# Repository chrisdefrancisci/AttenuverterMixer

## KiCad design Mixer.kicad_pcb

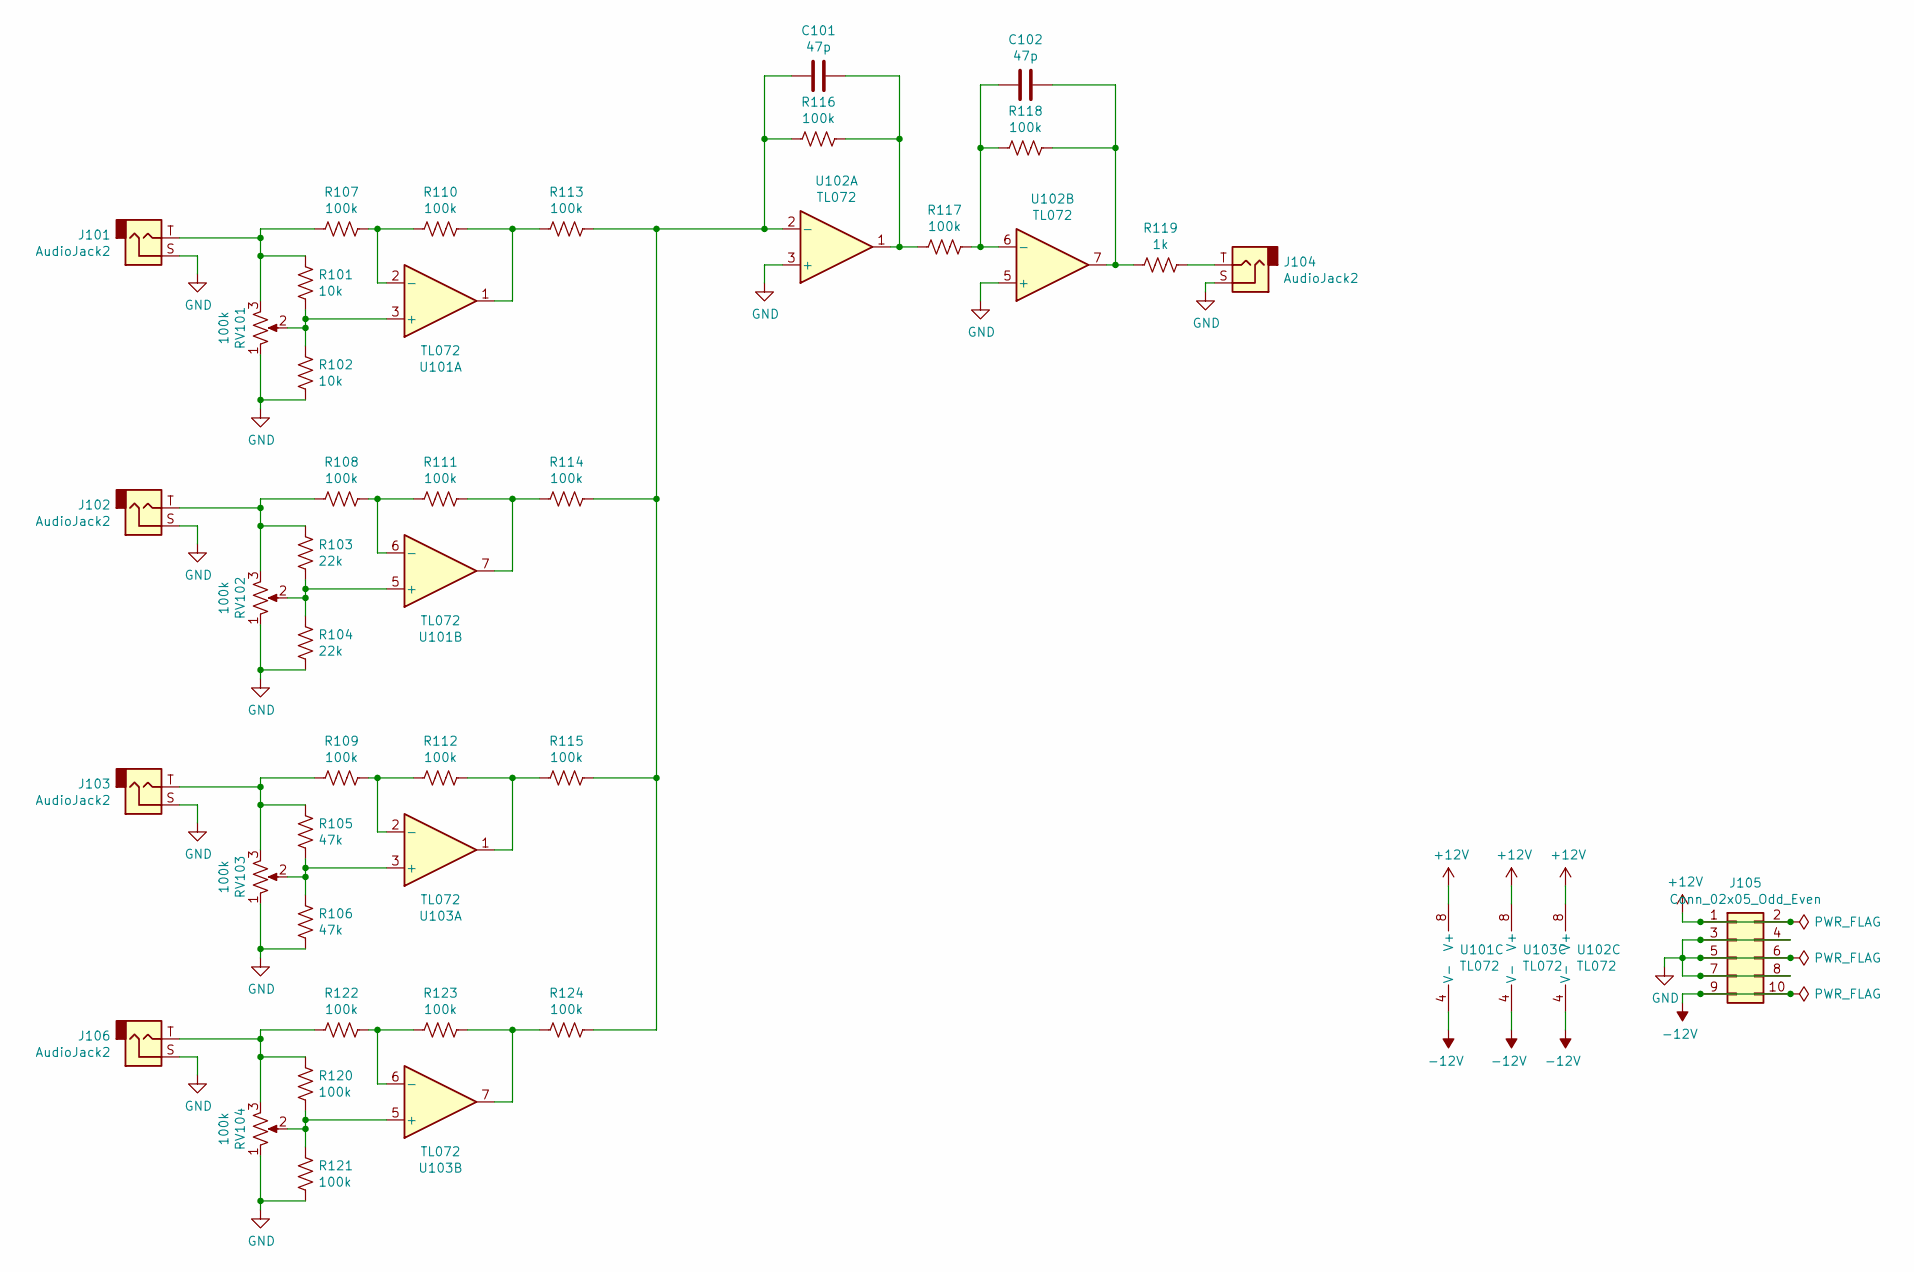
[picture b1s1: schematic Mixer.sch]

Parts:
C101, C102: 47p; C_0402_1005Metric; LCSC C1567
J101, J102, J103, J104, J106: AudioJack2; A-2563
J105: Conn_02x05_Odd_Even; PinHeader_2x05_P2.54mm_Vertical
R101, R102: 10k; R_0805_2012Metric; LCSC C17414
R103, R104: 22k; R_0805_2012Metric; LCSC C17560
R105, R106: 47k; R_0805_2012Metric; LCSC C17713
R107, R108, R109, R110, R111, R112, R113, R114, R115, R116, R117, R118, R120, R121, R122, R123, R124: 100k; R_0805_2012Metric; LCSC C17407
R119: 1k; R_0805_2012Metric; LCSC C17513
RV101, RV102, RV103, RV104: 100k; A-5513
U101, U102, U103: TL072; SOIC-8_3.9x4.9mm_P1.27mm; LCSC C6961

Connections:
+12V: J105.1, J105.2, U101.8 (V+), U102.8 (V+), U103.8 (V+)
-12V: J105.9, J105.10, U101.4 (V-), U102.4 (V-), U103.4 (V-)
GND: J101.S, J102.S, J103.S, J104.S, J105.3, J105.4, J105.5, J105.6, J105.7, J105.8, J106.S, R102.2, R104.2, R106.2, R121.2, RV101.1, RV102.1, RV103.1, RV104.1, U102.3 (+), U102.5 (+)
unnamed: C101.1, R116.1, R117.2, U102.1
unnamed: C101.2, R113.1, R114.1, R115.1, R116.2, R124.1, U102.2 (-)
unnamed: C102.1, R118.1, R119.2, U102.7
unnamed: C102.2, R117.1, R118.2, U102.6 (-)
unnamed: J101.T, R101.1, R107.2, RV101.3
unnamed: J102.T, R103.1, R108.2, RV102.3
unnamed: J103.T, R105.1, R109.2, RV103.3
unnamed: J104.T, R119.1
unnamed: J106.T, R120.1, R122.2, RV104.3
unnamed: R101.2, R102.1, RV101.2, U101.3 (+)
unnamed: R103.2, R104.1, RV102.2, U101.5 (+)
unnamed: R105.2, R106.1, RV103.2, U103.3 (+)
unnamed: R107.1, R110.2, U101.2 (-)
unnamed: R108.1, R111.2, U101.6 (-)
unnamed: R109.1, R112.2, U103.2 (-)
unnamed: R110.1, R113.2, U101.1
unnamed: R111.1, R114.2, U101.7
unnamed: R112.1, R115.2, U103.1
unnamed: R120.2, R121.1, RV104.2, U103.5 (+)
unnamed: R122.1, R123.2, U103.6 (-)
unnamed: R123.1, R124.2, U103.7

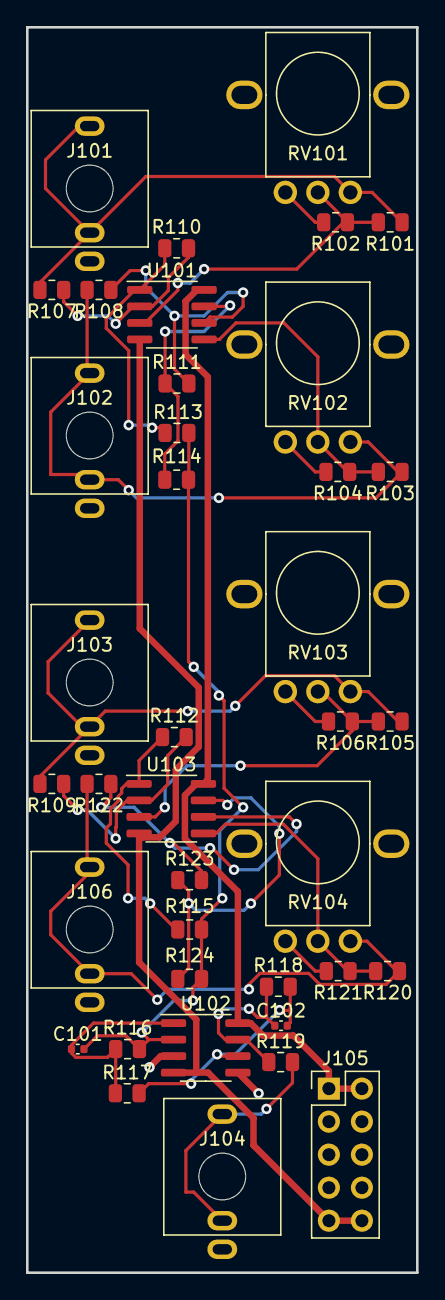
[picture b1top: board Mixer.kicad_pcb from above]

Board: 2 copper layers, 30.0 x 95.8 mm, 39 parts (0 on the bottom side), 24 nets.

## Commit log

2021-05-07 Initial layout in PCBNew
2021-05-10 Added attenuverters
2021-05-11 47pF caps and 100k resistors converted to SMD
2021-05-27 fixed op amp issue
